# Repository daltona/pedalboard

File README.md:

pedalboard
==========

The board:
<pre>
 _____________________________________
|     _______              _______    |
|    |_______|            |_______|   |
|                                     |
|    o      o      o      o      o    |
|   11     12     13     14     15    |
|                                     |
|    o      o      o      o      o    |
|    6      7      8      9     10    |
|                                     |
|    o      o      o      o      o    |
|    1      2      3      4      5    |
|_____________________________________|
</pre>

   * Left display is a 2x16 LCD 

     For configuration purpose

     This display is connected throught an I2C expander chip.

     The prototype is using a snootlab deuligne for now.

   * Right display is a 1x8 14digit Led display.

     For patch name display / Tuner display

     This display is connected with 3 GPIO in a Synchronous serial mode.

     http://www.embeddedadventures.com/14_segment_led_display_DSP-0801-BLUE.html

   * Buttons

     Arranged in a 3x15 matrix and uses Keypad library.

   * One Led per button.

     Connected throuh 74HC595 shift registers. 

     Use same SCLK / SDATA as the 14 digit led display with a second latch gpio.

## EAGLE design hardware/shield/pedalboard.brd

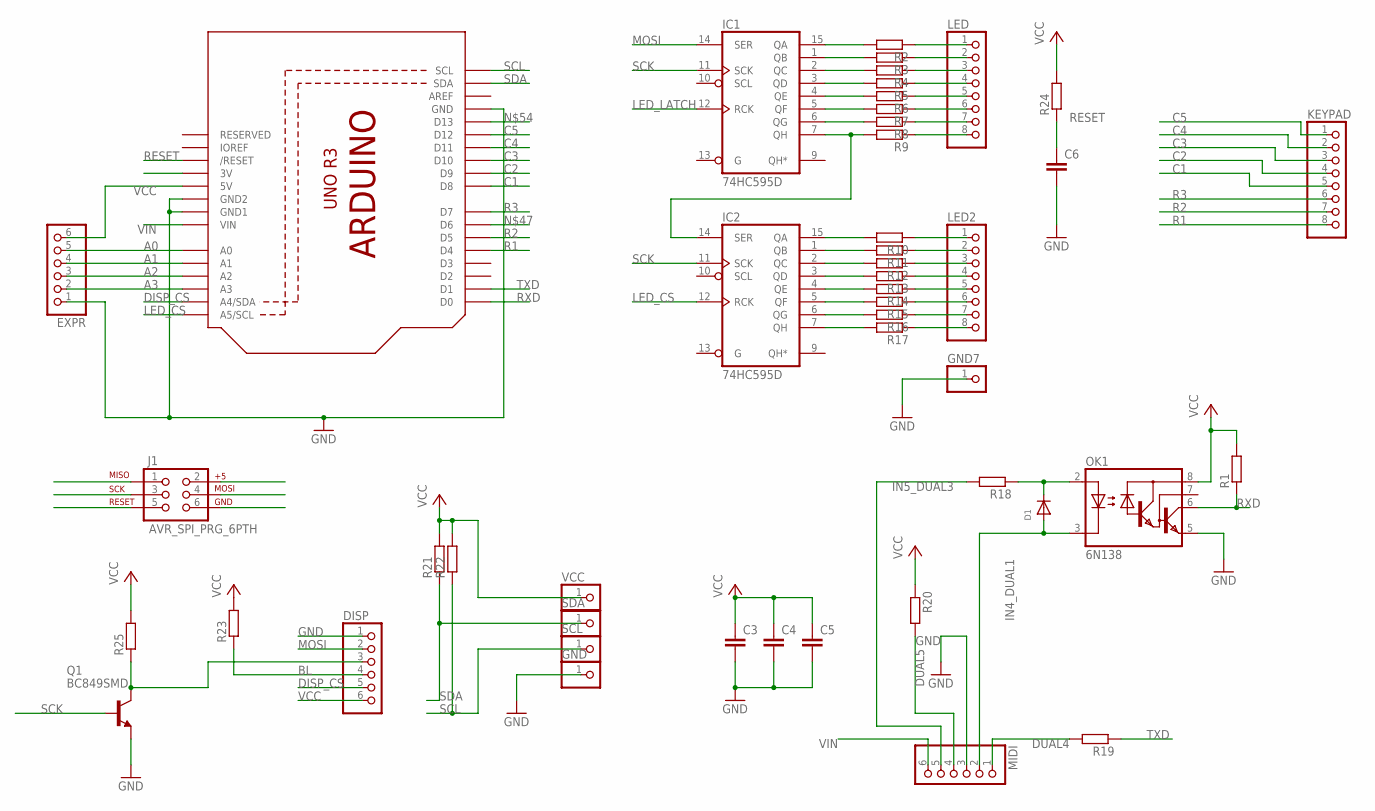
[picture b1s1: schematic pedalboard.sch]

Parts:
C3, C4, C6: CC0603; C0603
C5: C; C0805
D1: DIODEDO-1N4148; DO-1N4148
DISP: PINHD-1X6; 1X06
EXPR: PINHD-1X6; 1X06
GND, GND7: PINHD-1X1; 1X01
IC1, IC2: 74HC595D; SO16
J1: AVR_SPI_PRG_6PTH; 2X3
KEYPAD: PINHD-1X8CLEANBIG; 1X08-CLEANBIG
LED, LED2: PINHD-1X8CLEANBIG; 1X08-CLEANBIG
MIDI: PINHD-1X6; 1X06
OK1: 6N138; DIL08
Q1: BC849SMD; SOT23-BEC
R1, R2, R3, R4, R5, R6, R7, R8, R9, R10, R11, R12, R13, R14, R15, R16, R17, R18, R19, R20, R21, R22, R23, R24, R25: R-EU_R0805; R0805
SCL: PINHD-1X1; 1X01
SDA: PINHD-1X1; 1X01
U2: ARDUINOR3-BPLACE
VCC: PINHD-1X1; 1X01

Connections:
A0: EXPR.5, U2.A0
A1: EXPR.4, U2.A1
A2: EXPR.3, U2.A2
A3: EXPR.2, U2.A3
BL: DISP.4, R23.1
C1: KEYPAD.5, U2.D8
C2: KEYPAD.4, U2.D9
C3: KEYPAD.3, U2.D10
C4: KEYPAD.2, U2.D11
C5: KEYPAD.1, U2.D12
DISP_CS: DISP.5, U2.A4 (A4/SDA)
DUAL4: MIDI.1, R19.2
DUAL5: MIDI.4, R20.2
GND: C3.2, C4.2, C5.2, C6.2, DISP.1, EXPR.1, GND.1, GND7.1, IC1.8 (GND), IC2.8 (GND), J1.6, MIDI.3, OK1.5 (GND), Q1.E, U2.GND, U2.GND1, U2.GND2
IN4_DUAL1: D1.A, MIDI.2, OK1.3 (C)
IN5_DUAL3: MIDI.5, R18.2
LED2: LED2.1, R10.1
LED_CS: IC2.12 (RCK), U2.A5 (A5/SCL)
LED_LATCH: IC1.12 (RCK)
MISO: J1.1
MOSI: DISP.2, IC1.14 (SER), J1.4
unnamed: IC1.7 (QH), IC2.14 (SER), R9.2
unnamed: IC2.4 (QE), R14.2
unnamed: IC2.5 (QF), R15.2
unnamed: IC1.15 (QA), R2.2
unnamed: IC1.1 (QB), R3.2
unnamed: IC1.2 (QC), R4.2
unnamed: IC1.3 (QD), R5.2
unnamed: IC1.4 (QE), R6.2
unnamed: IC1.5 (QF), R7.2
unnamed: IC1.6 (QG), R8.2
unnamed: IC2.15 (QA), R10.2
unnamed: IC2.1 (QB), R11.2
unnamed: IC2.2 (QC), R12.2
unnamed: IC2.3 (QD), R13.2
unnamed: IC2.6 (QG), R16.2
unnamed: IC2.7 (QH), R17.2
unnamed: DISP.3, Q1.C, R25.1
unnamed: D1.C, OK1.2 (A), R18.1
unnamed: LED.1, R2.1
unnamed: LED.2, R3.1
unnamed: LED.3, R4.1
unnamed: LED.4, R5.1
unnamed: LED.5, R6.1
unnamed: LED.6, R7.1
unnamed: LED.7, R8.1
unnamed: LED.8, R9.1
unnamed: LED2.2, R11.1
unnamed: LED2.3, R12.1
unnamed: LED2.4, R13.1
unnamed: LED2.5, R14.1
unnamed: LED2.6, R15.1
unnamed: LED2.7, R16.1
unnamed: LED2.8, R17.1
R1: KEYPAD.8, U2.D4
R2: KEYPAD.7, U2.D5
R3: KEYPAD.6, U2.D7
RESET: C6.1, J1.5, R24.1, U2.RESET (/RESET)
RXD: OK1.6 (VO), R1.1, U2.D0
SCK: IC1.11 (SCK), IC2.11 (SCK), J1.3, Q1.B
SCL: R22.1, SCL.1, U2.SCL
SDA: R21.1, SDA.1, U2.SDA
TXD: R19.1, U2.D1
VCC: C3.1, C4.1, C5.1, DISP.6, EXPR.6, IC1.16 (VCC), IC2.16 (VCC), J1.2, OK1.8 (VCC), R1.2, R20.1, R21.2, R22.2, R23.2, R24.2, R25.2, U2.5V, VCC.1
VIN: MIDI.6, U2.VIN

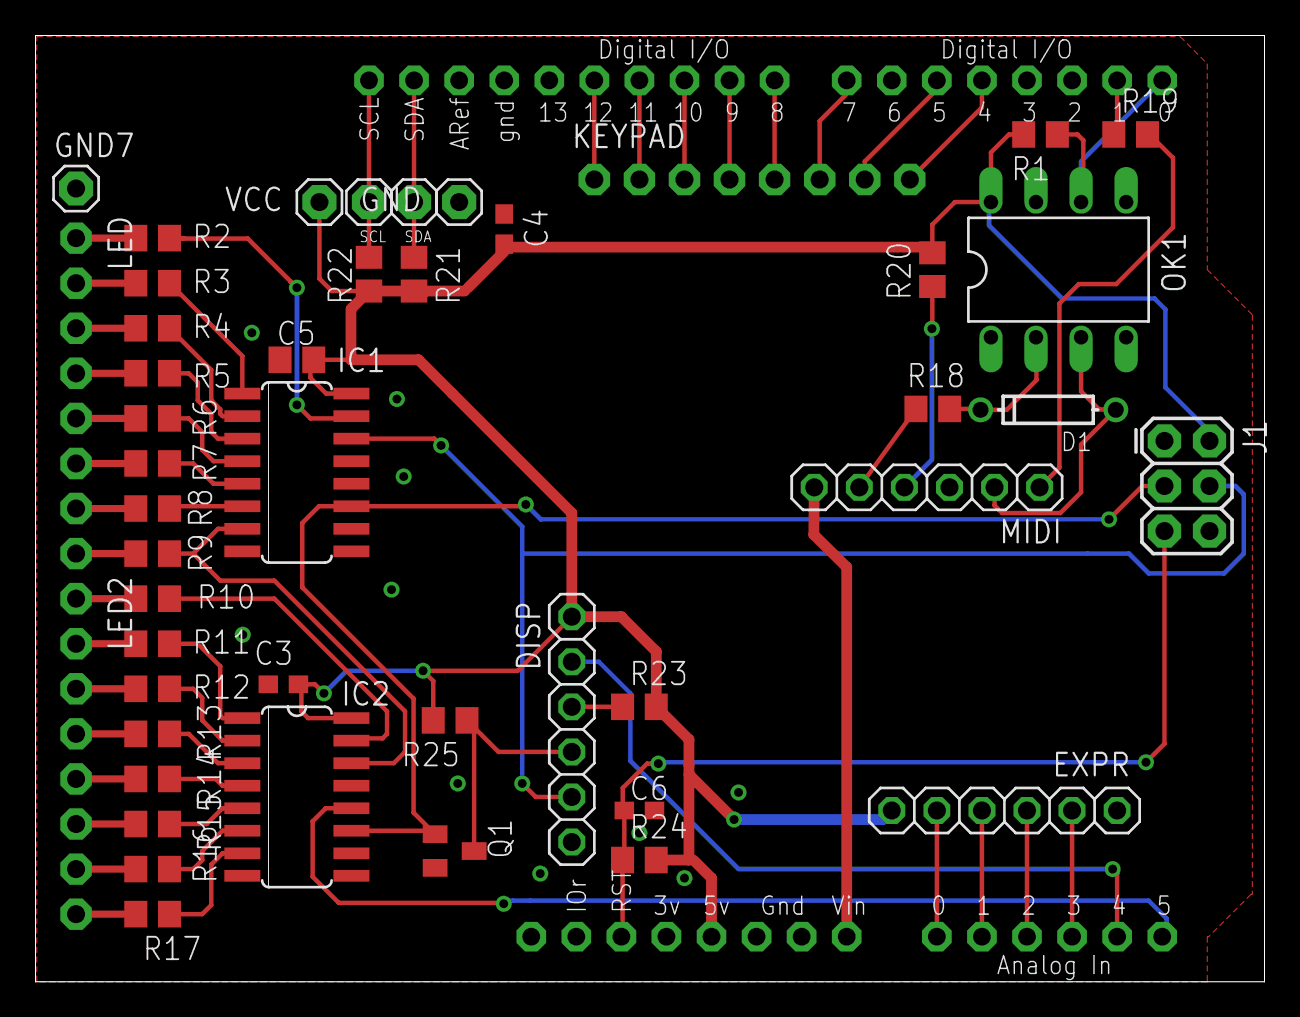
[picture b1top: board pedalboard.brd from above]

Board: 2 copper layers, 69.3 x 53.3 mm, 47 parts (0 on the bottom side), 63 nets.

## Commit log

2013-09-10 Add menu initial code.
2013-09-10 Main loop for menu
2013-09-10 Make it work
2013-09-11 Load all button data. Show last action performed in run mode.
2013-09-11 Refactor code.
2013-09-11 Fix compilation
2013-09-12 Format, add MIDI Handling
2013-09-12 Add expression pedal handling
2013-09-18 Add restoring expression pedal data
2013-09-18 Add support for 14segment display
2013-09-18 Add support for leds
2013-09-19 14seg display works.
2013-09-23 Use buttons for config
2013-09-23 Try to implement key hold
2013-09-23 Use default keys for menu
2013-09-24 Do not process the button selection through the edit menu
2013-09-24 Implement actual main menu. May not work :)
2013-09-25 Allow comming back to main menu
2013-09-25 14seg animation
2013-09-25 Update readme with more details.
2013-09-25 Move display to own file
2013-09-26 Add kemper definition file, start kemper sysex management
2013-09-27 Verified to work with kemper. Cool...
2013-09-28 Add request state and rig name
2013-10-02 Add expression pedals configuration menu
2013-10-03 Kemper feedback works
2014-07-04 Update to latest working version
2014-07-10 Update documentation
2014-07-10 Code size optimization
2014-12-15 Add front panel design
2015-01-16 hardware: add arduino shield cad

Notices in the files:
parts and their libraries:
SparkFun-Connectors: Licensing: CC v3.0 Share-Alike You are welcome to use this library for commercial purposes.
